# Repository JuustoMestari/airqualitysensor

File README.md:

# Air quality sensor
## Device
- ESP32 board : https://ebay.to/39Jhv0x
## Air quality sensor
- PMS7003 : https://download.kamami.com/p564008-p564008-PMS7003%20series%20data%20manua_English_V2.5.pdf
## Temperature/Humidity sensor
- DHT22 : https://www.sparkfun.com/datasheets/Sensors/Temperature/DHT22.pdf
## Pinout
| ESP32         | DHT22         | PMS7003     |
| ------------- |:-------------:| -----------:|
|VIN		        |               |             |
|GND		        |               |             |
|RST            |               |RST          |
|IO17		        |               |RX           |
|IO16		        |               |TX           |
|3V3	          |VCC            |VCC          |
|GND	          |GND            |GND          |	
|IO4            |DATA           |             |	

## Libraries
- Micro Web Server : https://github.com/jczic/MicroWebSrv
- pms7003+AQI : https://github.com/pkucmus/micropython-pms7003

## firmware
- Download latest version of micropython for ESP32 : http://micropython.org/download#esp32
- Flash using instructions from micropython firmware download website using esptool : https://github.com/espressif/esptool . Esptool requires python module "pyserial" (pip install pyserial)
```console
python esptool.py --chip esp32 --port COM3 erase_flash
```
```console
python esptool.py --chip esp32 --port COM3 --baud 460800 write_flash -z 0x1000 esp32-20190125-v1.xxxxx.bin
```

## rshell
Install with 
```console
sudo pip3 install rshell
```
```console
pip install rshell
```
List files on device
```console
rshell -p COM3 ls /pyboard
```
Clear files on device
```console
rshell -p COM3 rm -r /pyboard/
```
Copy all files to device (doesn't seem to work on windows)
```console
rshell -p COM3 cp -r device/* /pyboard
```
Copy single file at a time (windows)
```console
rshell -p COM3 cp main.py /pyboard
```

## serial
You can monitor what is going on with the device by connecting with a client like Putty.  
Set port (COMX or /dev/ttyUSBX) and speed to 115200. Press reset button (EN) on ESP32.

# TODO
- ~~sync time with ntp server~~
- ~~add DHT22 logic~~
- improve logic if pms7003 returns AQI of 0
- improve UI
  - ~~add gauges~~
  - ~~add time series (1 min, 10min, 30min, 1 hour)~~
  - ~~add current time~~
  - ~~add flash space~~
  - ~~use progressbar for flash space~~
  - automatically refresh UI every minute
  - ~~improve page's css so graph is responsive, using flex~~
  - Fix metric colors
  - ~~change graph scale depending on period (1,10,30,60)~~
  - ~~improve display on mobile~~

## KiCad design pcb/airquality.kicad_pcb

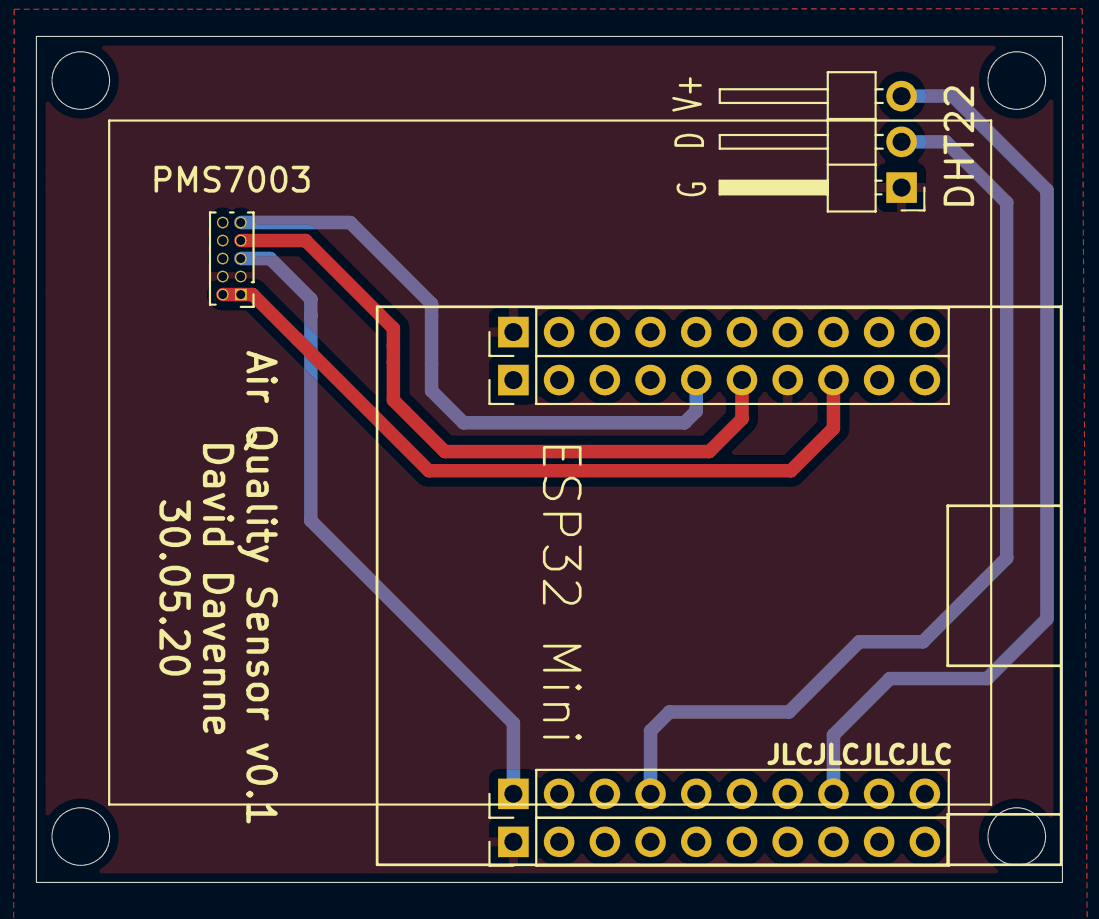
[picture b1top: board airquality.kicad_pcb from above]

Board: 2 copper layers, 57.0 x 47.0 mm, 3 parts (0 on the bottom side), 7 nets.

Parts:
DHT22: DHT22; PinHeader_1x03_P2.54mm_Horizontal
ESP32 Mini: ESP32_Wemos
PMS7003: PMS7003; PinHeader_2x05_P1.00mm_Vertical

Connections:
5V: ESP32 Mini.13, PMS7003.1, PMS7003.2
/3V3: DHT22.3, ESP32 Mini.28
/IO18: DHT22.2, ESP32 Mini.24
/RST: ESP32 Mini.21, PMS7003.5
/RX: ESP32 Mini.15, PMS7003.7
/TX: ESP32 Mini.16, PMS7003.9
GND: DHT22.1, ESP32 Mini.1, ESP32 Mini.14, ESP32 Mini.40, PMS7003.3, PMS7003.4

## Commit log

2020-01-07 init
2020-01-08 added extended sensors to README
2020-01-08 fix command
2020-02-07 update urequests logic, remove unecessary library
2020-02-07 add connections
2020-02-14 add mhz19b sensor
2020-02-14 add missing mhz19b
2020-02-18 add abc feature
2020-02-27 add pinout
2020-05-21 update to use pms7003 device
2020-05-22 add aggregate logic
2020-05-22 add ntp
2020-05-22 bug fixes
2020-05-22 bug fix, take first element of array instead of full array
2020-05-22 improve UI
2020-05-23 fix aggregation bug
2020-05-23 add gitignore for kicad files
2020-05-23 add freecad model and stl
2020-05-23 add kicad files
2020-05-23 update TODO
2020-05-23 fix aggregate to use average
2020-05-23 update pcb
2020-05-23 add dht logic
2020-05-24 add todo
2020-05-24 add garbage collector after aggregate
2020-05-24 remove gc
2020-05-24 add mobile css
2020-05-24 switch from 100 to 50 records
2020-05-26 add esp32 mini pinout
2020-06-13 add proper mobile display
2020-06-21 improve mobile style
2020-06-21 remove test data
2020-06-21 add pms7003 PDF
2020-06-22 add case cover
